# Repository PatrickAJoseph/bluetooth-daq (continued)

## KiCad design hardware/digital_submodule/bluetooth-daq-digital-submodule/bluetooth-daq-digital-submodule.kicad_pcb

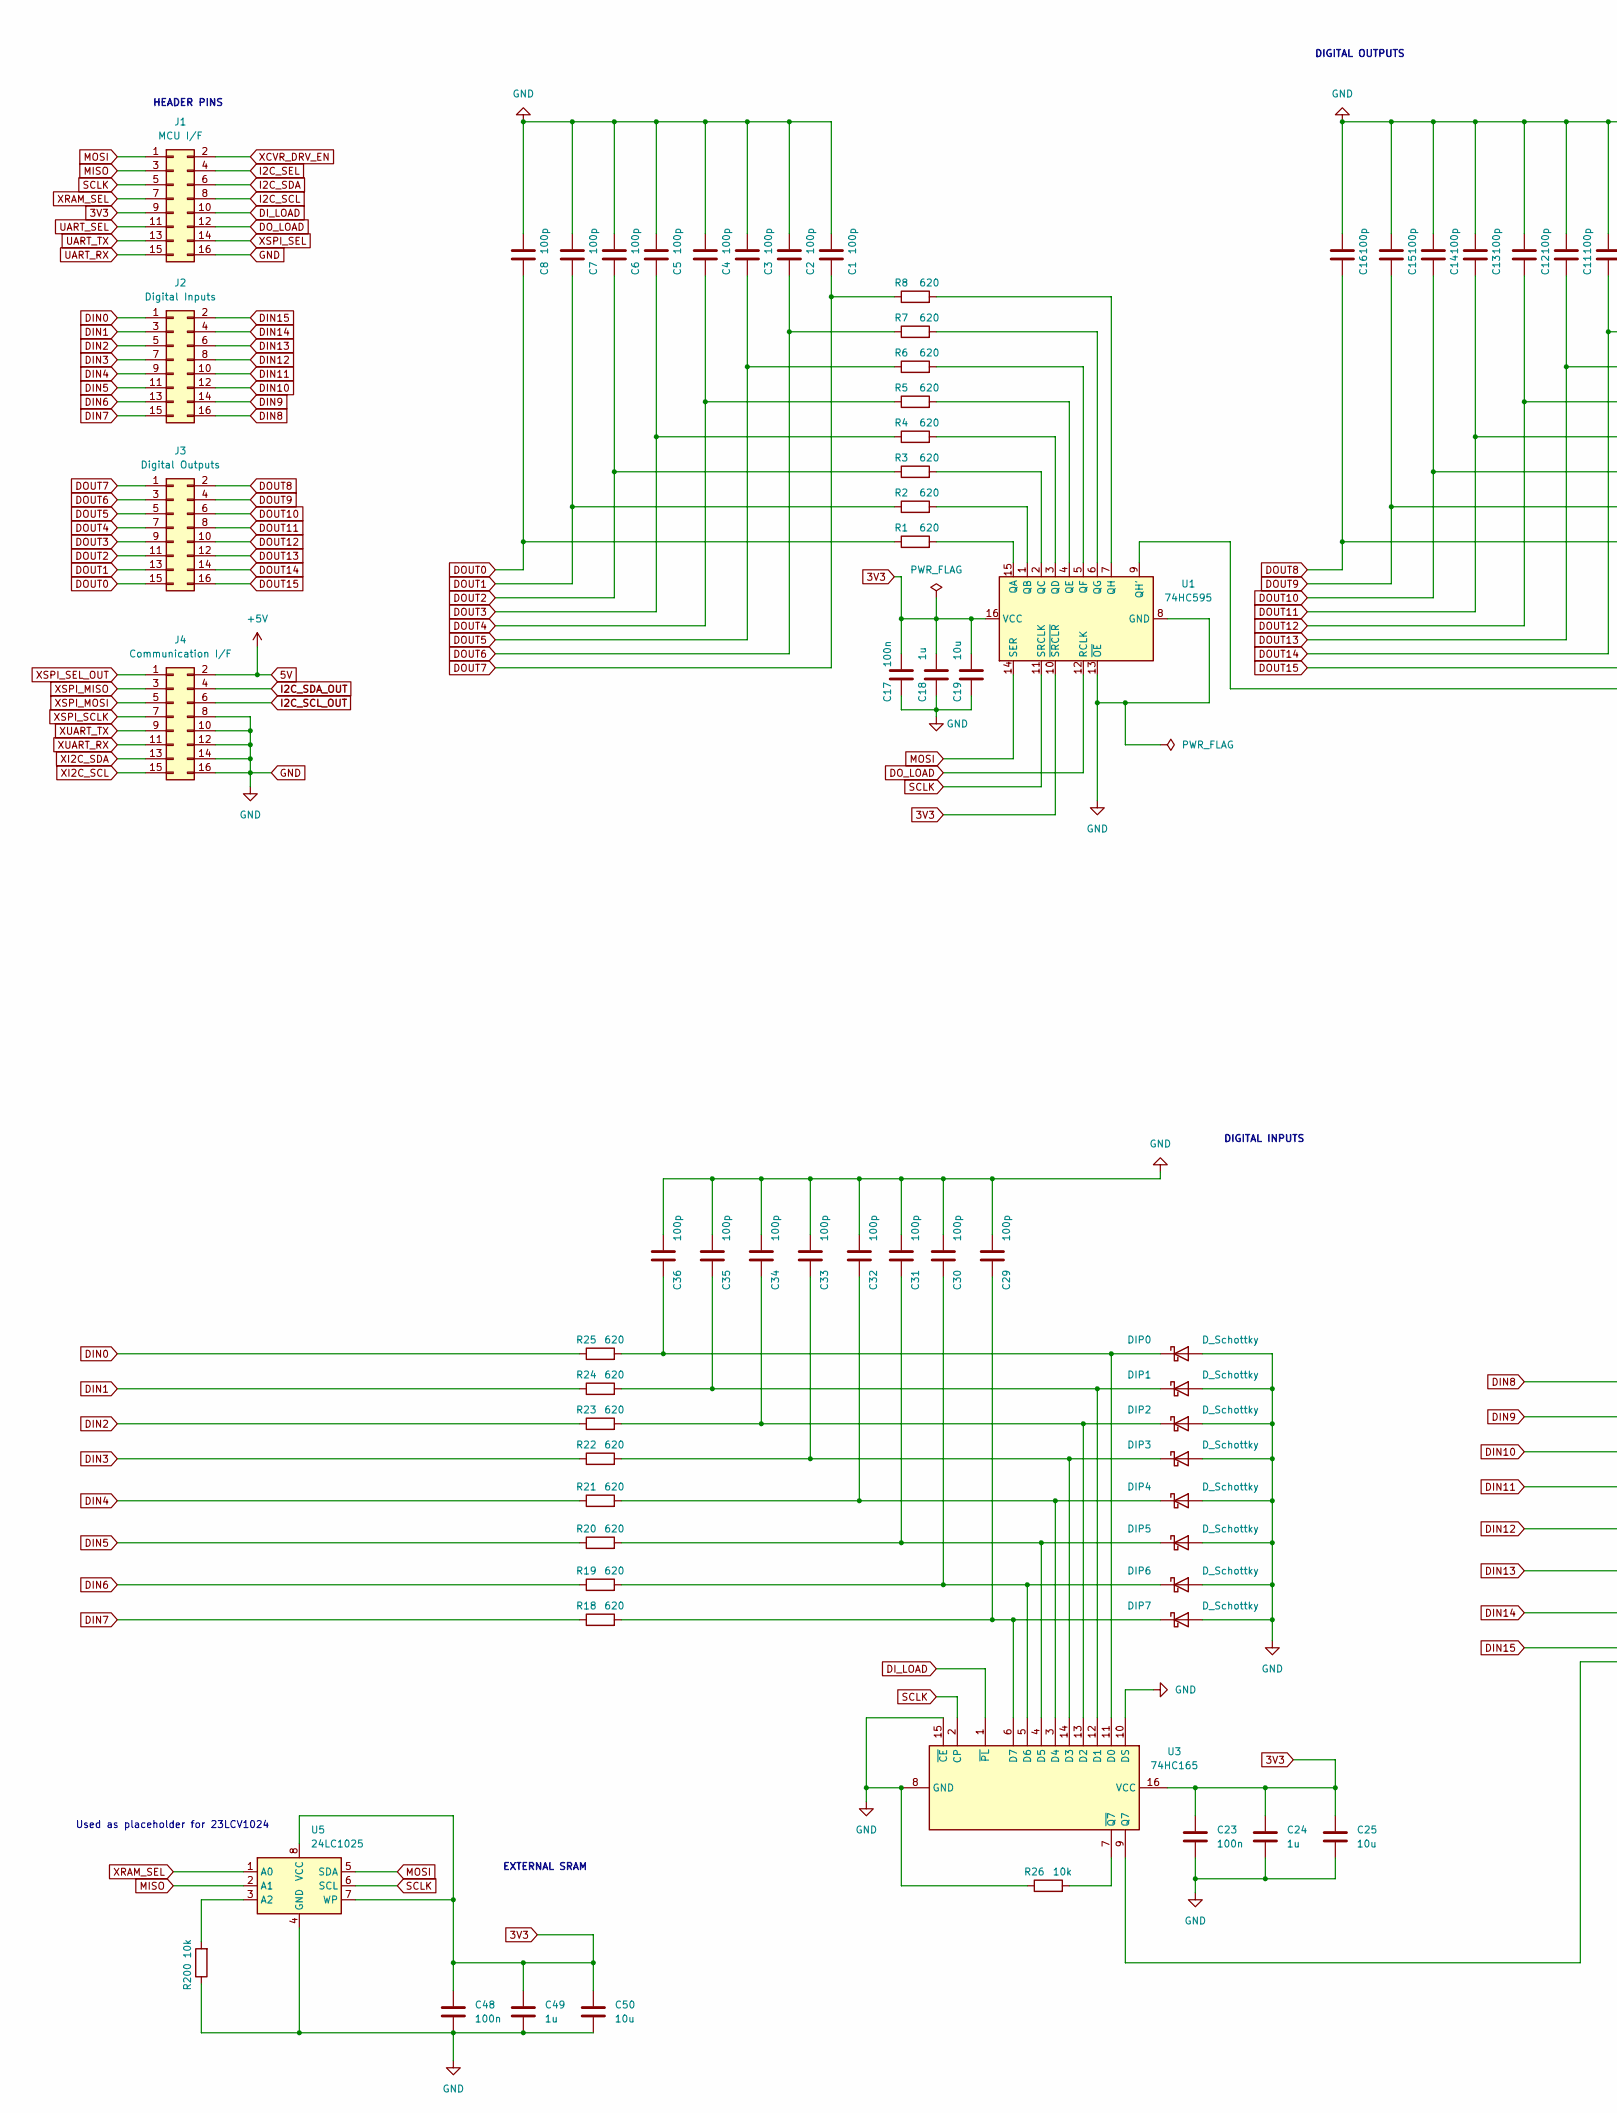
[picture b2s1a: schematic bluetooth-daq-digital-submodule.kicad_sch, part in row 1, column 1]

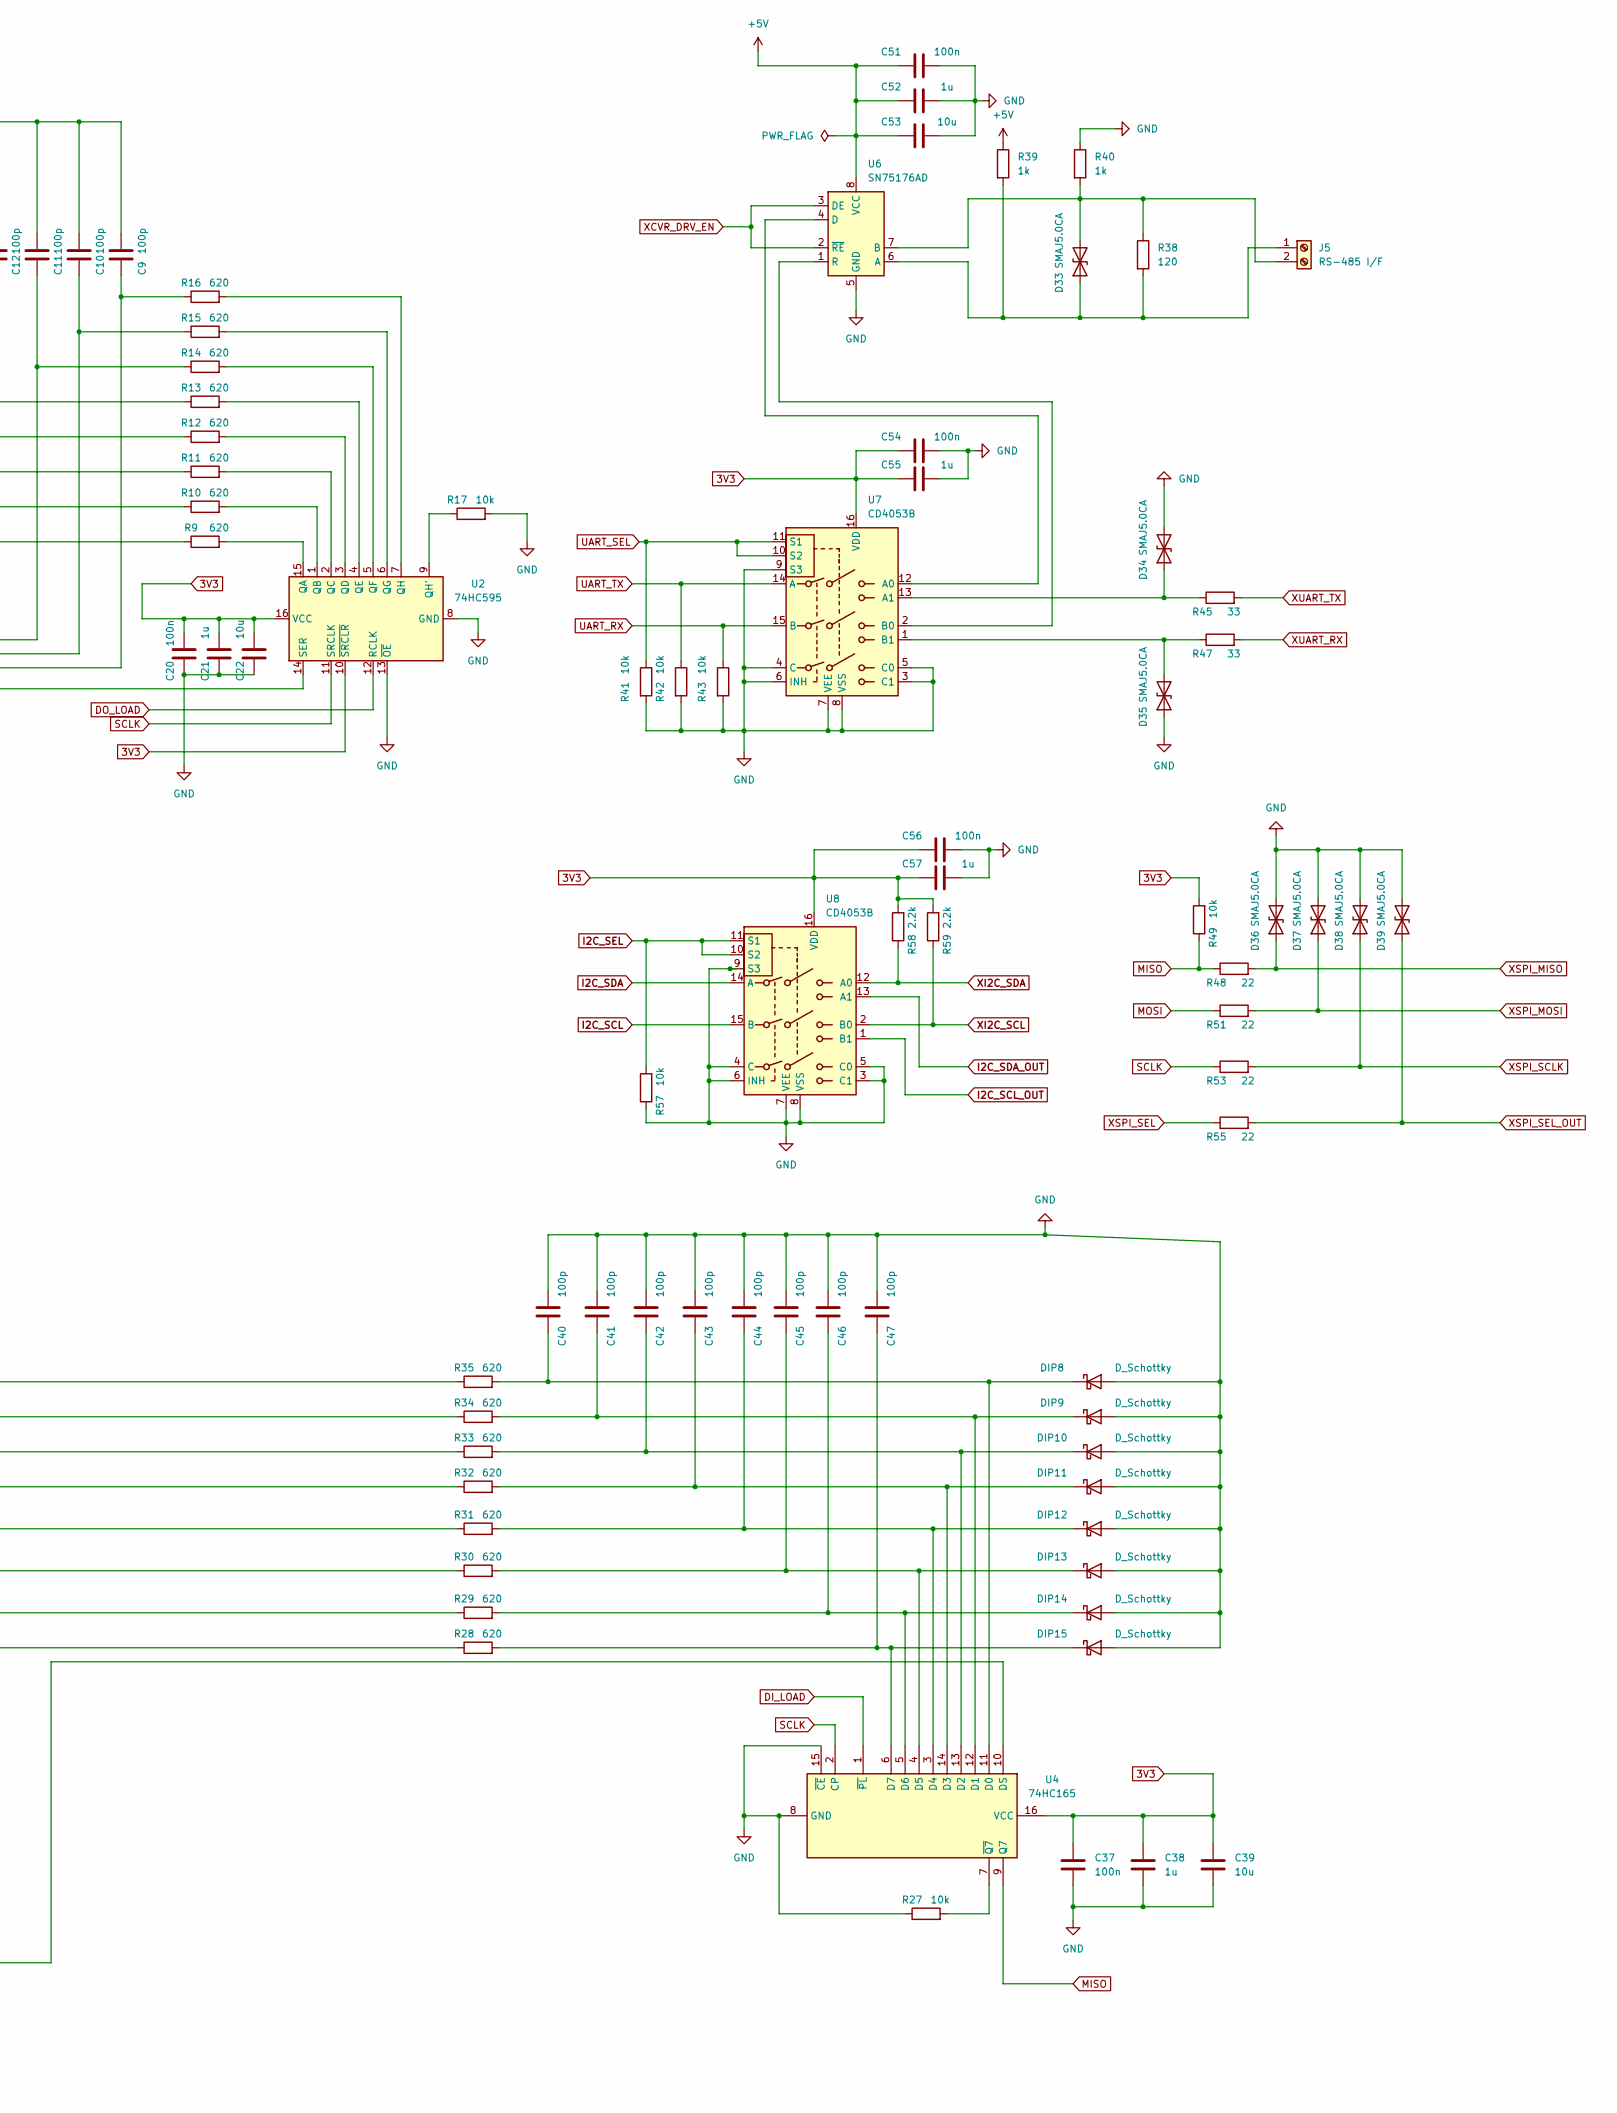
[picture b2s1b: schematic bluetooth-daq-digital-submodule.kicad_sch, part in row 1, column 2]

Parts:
C1, C2, C3, C4, C5, C6, C7, C8, C9, C10, C11, C12, C13, C14, C15, C16, C29, C30, C31, C32, C33, C34, C35, C36, C40, C41, C42, C43, C44, C45, C46, C47: 100p; C_0805_2012Metric_Pad1.18x1.45mm_HandSolder
C17, C20, C23, C37, C48, C51, C54, C56: 100n; C_0805_2012Metric_Pad1.18x1.45mm_HandSolder
C18, C21, C24, C38, C49, C52, C55, C57: 1u; C_0805_2012Metric_Pad1.18x1.45mm_HandSolder
C19, C22, C25, C39, C50, C53: 10u; C_0805_2012Metric_Pad1.18x1.45mm_HandSolder
D33, D34, D35, D36, D37, D38, D39: SMAJ5.0CA; D_SMA_Handsoldering
DIP0, DIP1, DIP2, DIP3, DIP4, DIP5, DIP6, DIP7, DIP8, DIP9, DIP10, DIP11, DIP12, DIP13, DIP14, DIP15: D_Schottky; D_SMA_Handsoldering
J1: MCU I/F; PinHeader_2x08_P2.54mm_Vertical
J2: Digital Inputs; PinHeader_2x08_P2.54mm_Vertical
J3: Digital Outputs; PinHeader_2x08_P2.54mm_Vertical
J4: Communication I/F; PinHeader_2x08_P2.54mm_Vertical
J5: RS-485 I/F; PhoenixContact_MCV_1,5_2-G-5.08_1x02_P5.08mm_Vertical
R1, R2, R3, R4, R5, R6, R7, R8, R9, R10, R11, R12, R13, R14, R15, R16, R18, R19, R20, R21, R22, R23, R24, R25, R28, R29, R30, R31, R32, R33, R34, R35: 620; R_0805_2012Metric_Pad1.20x1.40mm_HandSolder
R17, R26, R27, R41, R42, R43, R49, R57, R200: 10k; R_0805_2012Metric_Pad1.20x1.40mm_HandSolder
R38: 120; R_1206_3216Metric_Pad1.30x1.75mm_HandSolder
R39, R40: 1k; R_1206_3216Metric_Pad1.30x1.75mm_HandSolder
R45, R47: 33; R_0805_2012Metric_Pad1.20x1.40mm_HandSolder
R48, R51, R53, R55: 22; R_0805_2012Metric_Pad1.20x1.40mm_HandSolder
R58, R59: 2.2k; R_0805_2012Metric_Pad1.20x1.40mm_HandSolder
U1, U2: 74HC595; SOIC-16_3.9x9.9mm_P1.27mm
U3, U4: 74HC165; D16
U5: 24LC1025; SOIC8-N_MC_MCH
U6: SN75176AD; SOIC-8_3.9x4.9mm_P1.27mm
U7, U8: CD4053B; D16

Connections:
3V3: C17.1, C18.1, C19.1, C20.1, C21.1, C22.1, C23.1, C24.1, C25.1, C37.1, C38.1, C39.1, C48.1, C49.1, C50.1, C54.1, C55.1, C56.1, C57.1, J1.9, R49.2, R58.2, R59.2, U1.10 (~SRCLR), U1.16 (VCC), U2.10 (~SRCLR), U2.16 (VCC), U3.16 (VCC), U4.16 (VCC), U5.7 (WP), U5.8 (VCC), U7.16 (VDD), U8.16 (VDD)
5V: C51.1, C52.1, C53.1, J4.2, R39.1, U6.8 (VCC)
DIN0: J2.1, R25.1
DIN1: J2.3, R24.1
DIN2: J2.5, R23.1
DIN3: J2.7, R22.1
DIN4: J2.9, R21.1
DIN5: J2.11, R20.1
DIN6: J2.13, R19.1
DIN7: J2.15, R18.1
DIN8: J2.16, R35.1
DIN9: J2.14, R34.1
DIN10: J2.12, R33.1
DIN11: J2.10, R32.1
DIN12: J2.8, R31.1
DIN13: J2.6, R30.1
DIN14: J2.4, R29.1
DIN15: J2.2, R28.1
DI_LOAD: J1.10, U3.1 (~PL), U4.1 (~PL)
DOUT0: C8.2, J3.15, R1.1
DOUT1: C7.2, J3.13, R2.1
DOUT2: C6.2, J3.11, R3.1
DOUT3: C5.2, J3.9, R4.1
DOUT4: C4.2, J3.7, R5.1
DOUT5: C3.2, J3.5, R6.1
DOUT6: C2.2, J3.3, R7.1
DOUT7: C1.2, J3.1, R8.1
DOUT8: C16.2, J3.2, R9.1
DOUT9: C15.2, J3.4, R10.1
DOUT10: C14.2, J3.6, R11.1
DOUT11: C13.2, J3.8, R12.1
DOUT12: C12.2, J3.10, R13.1
DOUT13: C11.2, J3.12, R14.1
DOUT14: C10.2, J3.14, R15.1
DOUT15: C9.2, J3.16, R16.1
DO_LOAD: J1.12, U1.12 (RCLK), U2.12 (RCLK)
GND: C1.1, C2.1, C3.1, C4.1, C5.1, C6.1, C7.1, C8.1, C9.1, C10.1, C11.1, C12.1, C13.1, C14.1, C15.1, C16.1, C17.2, C18.2, C19.2, C20.2, C21.2, C22.2, C23.2, C24.2, C25.2, C29.1, C30.1, C31.1, C32.1, C33.1, C34.1, C35.1, C36.1, C37.2, C38.2, C39.2, C40.1, C41.1, C42.1, C43.1, C44.1, C45.1, C46.1, C47.1, C48.2, C49.2, C50.2, C51.2, C52.2, C53.2, C54.2, C55.2, C56.2, C57.2, D34.2 (A2), D35.1 (A1), D36.2 (A2), D37.2 (A2), D38.2 (A2), D39.2 (A2), DIP0.2 (A), DIP1.2 (A), DIP2.2 (A), DIP3.2 (A), DIP4.2 (A), DIP5.2 (A), DIP6.2 (A), DIP7.2 (A), DIP8.2 (A), DIP9.2 (A), DIP10.2 (A), DIP11.2 (A), DIP12.2 (A), DIP13.2 (A), DIP14.2 (A), DIP15.2 (A), J1.16, J4.8, J4.10, J4.12, J4.14, J4.16, R17.2, R26.1, R27.1, R40.1, R41.2, R42.2, R43.2, R57.1, R200.1, U1.8 (GND), U1.13 (~OE), U2.8 (GND), U2.13 (~OE), U3.8 (GND), U3.10 (DS), U3.15 (~CE), U4.8 (GND), U4.15 (~CE), U5.4 (GND), U6.5 (GND), U7.3 (C1), U7.4 (C), U7.5 (C0), U7.6 (INH), U7.7 (VEE), U7.8 (VSS), U7.9 (S3), U8.3 (C1), U8.4 (C), U8.5 (C0), U8.6 (INH), U8.7 (VEE), U8.8 (VSS), U8.9 (S3)
I2C_SCL: J1.8, U8.15 (B)
I2C_SCL_OUT: J4.6, U8.1 (B1)
I2C_SDA: J1.6, U8.14 (A)
I2C_SDA_OUT: J4.4, U8.13 (A1)
I2C_SEL: J1.4, R57.2, U8.10 (S2), U8.11 (S1)
MISO: J1.3, R48.1, R49.1, U4.9 (Q7), U5.2 (A1)
MOSI: J1.1, R51.1, U1.14 (SER), U5.5 (SDA)
unnamed: C29.2, DIP7.1 (K), R18.2, U3.6 (D7)
unnamed: C30.2, DIP6.1 (K), R19.2, U3.5 (D6)
unnamed: C31.2, DIP5.1 (K), R20.2, U3.4 (D5)
unnamed: C32.2, DIP4.1 (K), R21.2, U3.3 (D4)
unnamed: C33.2, DIP3.1 (K), R22.2, U3.14 (D3)
unnamed: C34.2, DIP2.1 (K), R23.2, U3.13 (D2)
unnamed: C35.2, DIP1.1 (K), R24.2, U3.12 (D1)
unnamed: C36.2, DIP0.1 (K), R25.2, U3.11 (D0)
unnamed: C40.2, DIP8.1 (K), R35.2, U4.11 (D0)
unnamed: C41.2, DIP9.1 (K), R34.2, U4.12 (D1)
unnamed: C42.2, DIP10.1 (K), R33.2, U4.13 (D2)
unnamed: C43.2, DIP11.1 (K), R32.2, U4.14 (D3)
unnamed: C44.2, DIP12.1 (K), R31.2, U4.3 (D4)
unnamed: C45.2, DIP13.1 (K), R30.2, U4.4 (D5)
unnamed: C46.2, DIP14.1 (K), R29.2, U4.5 (D6)
unnamed: C47.2, DIP15.1 (K), R28.2, U4.6 (D7)
unnamed: D33.1 (A1), J5.1, R38.2, R39.2, U6.6 (A)
unnamed: D33.2 (A2), J5.2, R38.1, R40.2, U6.7 (B)
unnamed: D34.1 (A1), R45.1, U7.13 (A1)
unnamed: D35.2 (A2), R47.1, U7.1 (B1)
unnamed: R1.2, U1.15 (QA)
unnamed: R2.2, U1.1 (QB)
unnamed: R3.2, U1.2 (QC)
unnamed: R4.2, U1.3 (QD)
unnamed: R5.2, U1.4 (QE)
unnamed: R6.2, U1.5 (QF)
unnamed: R7.2, U1.6 (QG)
unnamed: R8.2, U1.7 (QH)
unnamed: R9.2, U2.15 (QA)
unnamed: R10.2, U2.1 (QB)
unnamed: R11.2, U2.2 (QC)
unnamed: R12.2, U2.3 (QD)
unnamed: R13.2, U2.4 (QE)
unnamed: R14.2, U2.5 (QF)
unnamed: R15.2, U2.6 (QG)
unnamed: R16.2, U2.7 (QH)
unnamed: R17.1, U2.9 (QH')
unnamed: R26.2, U3.7 (~Q7)
unnamed: R27.2, U4.7 (~Q7)
unnamed: R200.2, U5.3 (A2)
unnamed: U1.9 (QH'), U2.14 (SER)
unnamed: U3.9 (Q7), U4.10 (DS)
unnamed: U6.1 (R), U7.2 (B0)
unnamed: U6.4 (D), U7.12 (A0)
SCLK: J1.5, R53.1, U1.11 (SRCLK), U2.11 (SRCLK), U3.2 (CP), U4.2 (CP), U5.6 (SCL)
UART_RX: J1.15, R43.1, U7.15 (B)
UART_SEL: J1.11, R41.1, U7.10 (S2), U7.11 (S1)
UART_TX: J1.13, R42.1, U7.14 (A)
XCVR_DRV_EN: J1.2, U6.2 (~RE), U6.3 (DE)
XI2C_SCL: J4.15, R59.1, U8.2 (B0)
XI2C_SDA: J4.13, R58.1, U8.12 (A0)
XRAM_SEL: J1.7, U5.1 (A0)
XSPI_MISO: D36.1 (A1), J4.3, R48.2
XSPI_MOSI: D37.1 (A1), J4.5, R51.2
XSPI_SCLK: D38.1 (A1), J4.7, R53.2
XSPI_SEL: J1.14, R55.1
XSPI_SEL_OUT: D39.1 (A1), J4.1, R55.2
XUART_RX: J4.11, R47.2
XUART_TX: J4.9, R45.2

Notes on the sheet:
EXTERNAL SRAM
HEADER PINS
DIGITAL INPUTS
DIGITAL OUTPUTS
Used as placeholder for 23LCV1024

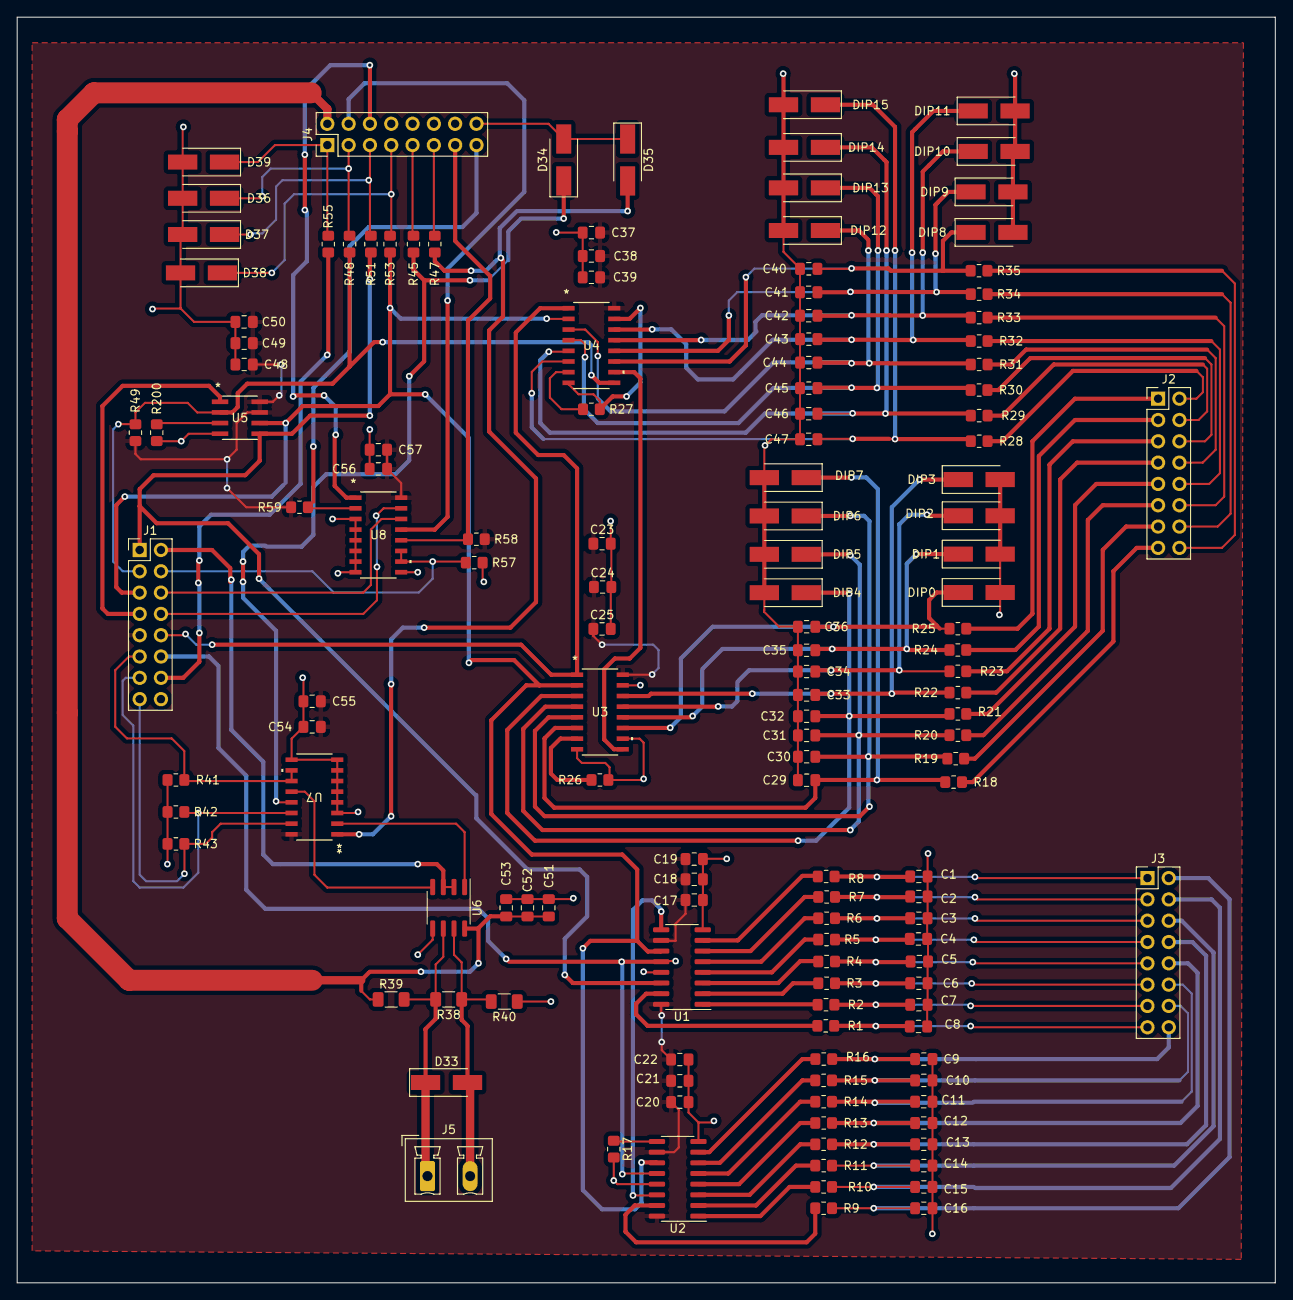
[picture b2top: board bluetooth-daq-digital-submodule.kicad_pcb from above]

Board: 2 copper layers, 150.0 x 150.9 mm, 142 parts (0 on the bottom side), 103 nets.

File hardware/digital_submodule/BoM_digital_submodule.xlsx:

Component label | Component value | Component name | Quantity | Footprint / package / size | Purchase link
U1, U2 |  | SN74HC595D | 4 | SOIC(D) 16 | SN74HC595D Texas Instruments | Integrated Circuits (ICs) | DigiKey
U3, U4 |  | SN74HC165D | 4 | SOIC(D) 16 | SN74HC165D Texas Instruments | Integrated Circuits (ICs) | DigiKey Marketplace
U7, U8 |  | CD4053BM | 4 | SOIC(D) 16 | CD4053BM Texas Instruments | Integrated Circuits (ICs) | DigiKey Marketplace
U5 |  | 23LCV1024 | 2 | SOIC-8 | 23LCV1024-I/SN Microchip Technology | Integrated Circuits (ICs) | DigiKey
U6 |  | SN75176ADR | 2 | SOIC-8 | SN75176ADR Texas Instruments | Integrated Circuits (ICs) | DigiKey
R1,R2,R3,R4,R5,R6,R7,R8,R9,R10,R11,R12,R13,R14,R15,R16,R17,R18,R19,R20,R21,R22,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 | 620E, 1/4W | SMD resistor | 40 | SMD_0805 | RC0805JR-07620RL YAGEO | Resistors | DigiKey
R200, R26, R17, R41, R42, R43, R57, R27, R49 | 10k, 1/4W | SMD resistor | 20 | SMD_0805 | CRCW080510K0JNEA Vishay Dale | Resistors | DigiKey
R48, R51, R53, R55 | 22E, 1/4W | SMD resistor | 10 | SMD_0805 | CR0805-JW-220ELF Bourns Inc. | Resistors | DigiKey
D36, D37, D38, D39, D35, D34, D33 |  | SMAJ5.0CA | 20 | DO_214AC | SMAJ5.0CA Shenzhen Slkormicro Semicon Co., Ltd. | Circuit Protection | DigiKey
R39, R40 | 1k, 1/4W | SMD resistor | 10 | SMD_0805 | Generic
R38 | 120E, 1/4W | SMD resistor | 5 | SMD_1206 | Generic
R58, R59 | 2.2k, 1/4W | SMD resistor | 10 | SMD_0805 | Generic
C1,C2,C3,C4,C5,C6,C7,C8,C9,C10,C11,C12,C13,C14,C15,C16,C29,C30,C31,C32,C33,C34,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 | 100pF, 50V, ceramic | SMD capacitor | 40 | SMD_0805 | Generic
DIP0, DIP1, DIP2, DIP3, DIP4, DIP5,DIP6, DIP7, DIP8, DIP9, DIP10, DIP11, DIP12,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 | 1A, 40V, SS14, Schottky diode | SS14 / Schottky Diode | 30 | DO_214AC | SS14 onsemi | Discrete Semiconductor Products | DigiKey
C48, C17, C23, C20, C51, C54, C56, C37 | 100nF, 50v, ceramic | SMD capacitor | 20 | SMD_0805 | Generic
C49, C18, C24, C21, C52, C55, C57, C36 | 1u, 50V, ceramic | SMD capacitor | 20 | SMD_0805 | Generic
C50, C19, C25, C22, C53, C39 | 10u, 50V, ceramic | SMD capacitor | 20 | SMD_0805 | Generic

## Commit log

2026-02-01 Modified README.md and added docs and hardware directories
2026-02-01 Removed hardware and software block diagram from README.md
2026-02-01 Added images for hardware & software block diagram
2026-02-01 Added hardware block diagram explanation
2026-02-01 Added software block diagram description
2026-02-02 Added hardware block diagrams for digital input and digital output hardware modules
2026-02-03 docs: Added hardware block diagram for low voltage analog inputs and HV voltage and current inputs.
2026-02-07 Added analog output section block diagram and power supply chain block diagrams
2026-02-07 Added initial schematics for digital submodule
2026-02-07 Addressed errors raised by KiCAD for digital sub-module.
2026-02-08 Added footprints for components in digital_submodule
2026-02-08 Arranged components in PCB view according their functionality
2026-02-09 Decided on component arangement for digital input and digital output sections of the digital submodule.
2026-02-09 Decided on initial component placement for digital submodule.
2026-02-09 Performed initial routing for digital submodule
2026-02-10 Routed digital output 1 of digital submodule
2026-02-11 Performed routing for interface section for digital submodule.
2026-02-11 Completed initial routing of digital sub module
2026-02-12 Performed first successful initial PCB routing
2026-02-12 Resolved PCB design errors
2026-02-15 Added Gerber files
2026-03-08 Added schematics and BoM
2026-03-09 Added simulations for LV & HV voltage sensing AFE
2026-03-22 Added analog submodule design
2026-03-22 Added PCB terminal labels
2026-03-22 Added initial CCS project with SysConfig settings for digital submodule
2026-03-24 DIO driver design doc V0
2026-03-24 DIO Design Doc V1
2026-03-25 Added code for PCB validation for XUART & XSPI
2026-03-25 Added i2c & RS485 interface test codes
2026-03-29 Completed PCB design for analog submodule
2026-03-30 Cleaned up resource management strategy
2026-03-30 Added SSCP handle for RS485 interface
2026-03-31 Added GPIO and SPI control support via SSCP stack
2026-04-01 Added skeleton for UART control via SSCP stack
2026-04-01 Added SSCP stack support for I2C & UART
2026-04-03 Added initial draft of DAQ Python module documentation
2026-04-04 Updated Python README.md for GPIO APIs
2026-04-04 Added APIs for I2C and SPI sudmodules in python/README.md
2026-04-05 Added Python module for GPIO sub-component
2026-04-05 Added I2C module in Python
2026-04-05 Added apis for uart
2026-04-05 Added basic apis for i2c
2026-04-06 Added uart, spi and i2c functional APIs
2026-04-07 Added tests for SPI, UART, I2C and GPIO Python drivers
2026-05-02 Added high speed data acquisition code and Python script
